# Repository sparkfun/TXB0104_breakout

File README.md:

SparkFun Voltage-Level Translator Breakout - TXB0104
================

[![SparkFun Voltage-Level Translator Breakout - TXB0104
](https://cdn.sparkfun.com//assets/parts/8/0/0/6/11771-01.jpg)](https://www.sparkfun.com/products/11771)

[SparkFun Voltage-Level Translator Breakout - TXB0104 (BOB-11771)](https://www.sparkfun.com/products/11771)

TI's bidirectional level translation IC.

Repository Contents
-------------------

* **/Hardware** - Eagle design files (.brd, .sch)
* **/Production** - Production panel files (.brd)

Documentation
--------------

* **[Hookup Guide](https://learn.sparkfun.com/tutorials/txb0104-level-shifter-hookup-guide)** - Basic hookup guide

License Information
-------------------

This product is _**open source**_! 

Please review the LICENSE.md file for license information. 

If you have any questions or concerns on licensing, please contact technical support on our [SparkFun forums](https://forum.sparkfun.com/viewforum.php?f=152).

Distributed as-is; no warranty is given.

- Your friends at SparkFun.

_<COLLABORATION CREDIT>_

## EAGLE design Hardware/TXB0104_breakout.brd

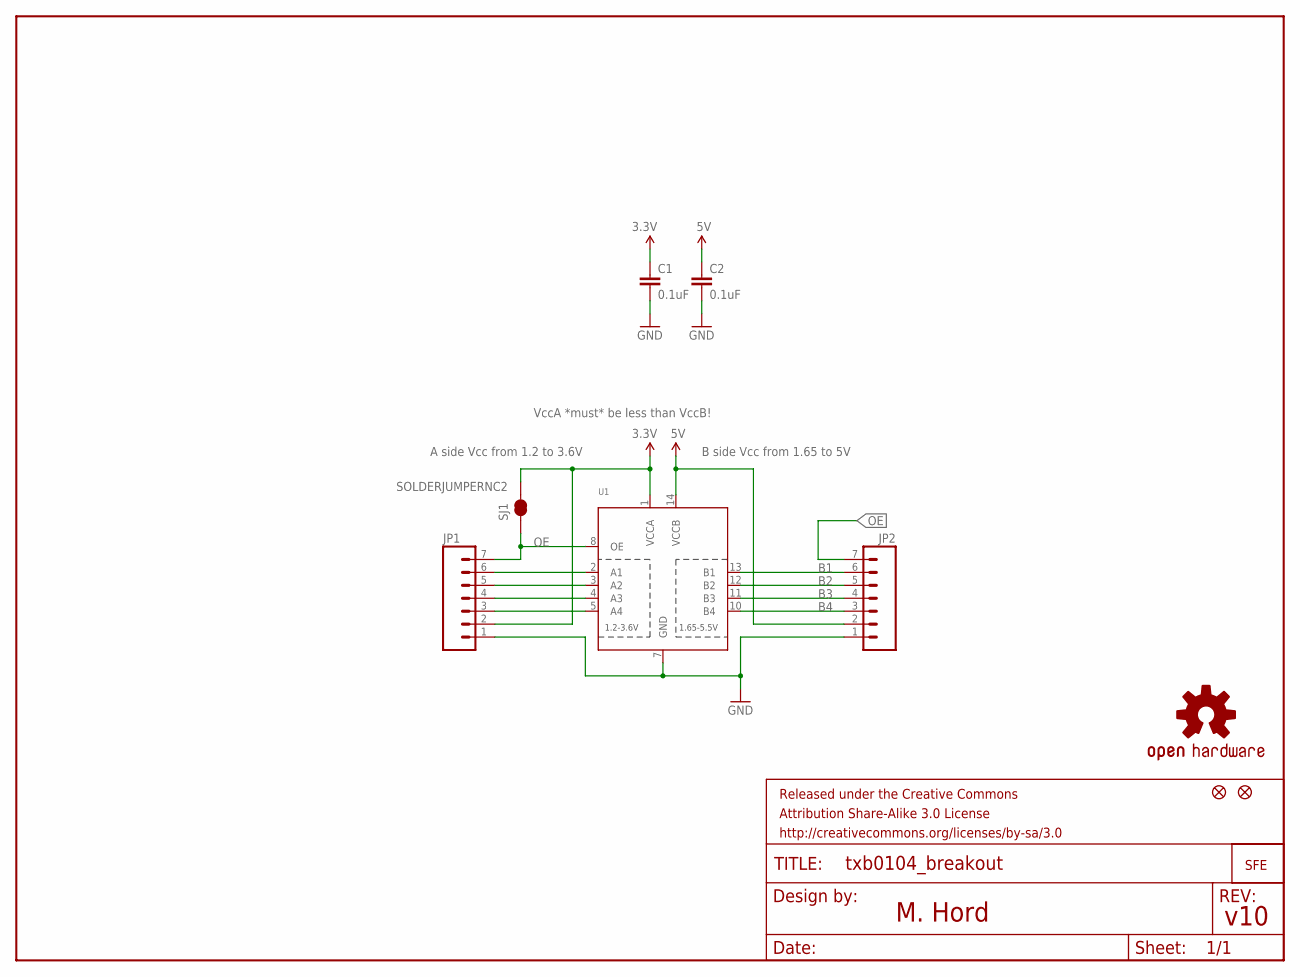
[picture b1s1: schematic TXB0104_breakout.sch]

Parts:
C1, C2: 0.1uF; 0603-CAP
FID1, FID2: FIDUCIALUFIDUCIAL; MICRO-FIDUCIAL
FRAME1: FRAME-LETTER; CREATIVE_COMMONS
JP1, JP2: M07; 1X07
LOGO1: LOGO-SFESK; SFE-LOGO-FLAME
LOGO2: OSHW-LOGOS; OSHW-LOGO-S
SJ1: SOLDERJUMPERNC2; SJ_2S-NOTRACE
U1: TXB0104PWRSOIC14; SO14

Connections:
3.3V: C1.1, JP1.2, SJ1.2, U1.1 (VCCA)
5V: C2.1, JP2.2, U1.14 (VCCB)
B1: JP2.6, U1.13 (B1)
B2: JP2.5, U1.12 (B2)
B3: JP2.4, U1.11 (B3)
B4: JP2.3, U1.10 (B4)
GND: C1.2, C2.2, JP1.1, JP2.1, U1.7 (GND)
unnamed: JP1.3, U1.5 (A4)
unnamed: JP1.4, U1.4 (A3)
unnamed: JP1.5, U1.3 (A2)
unnamed: JP1.6, U1.2 (A1)
OE: JP1.7, JP2.7, SJ1.1, U1.8 (OE)

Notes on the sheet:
A side Vcc from 1.2 to 3.6V
B side Vcc from 1.65 to 5V
VccA *must* be less than VccB!
v10
M. Hord

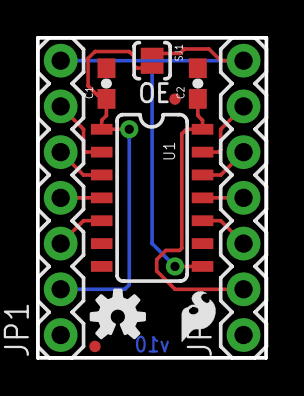
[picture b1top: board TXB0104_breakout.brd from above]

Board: 2 copper layers, 12.7 x 17.8 mm, 11 parts (0 on the bottom side), 12 nets.

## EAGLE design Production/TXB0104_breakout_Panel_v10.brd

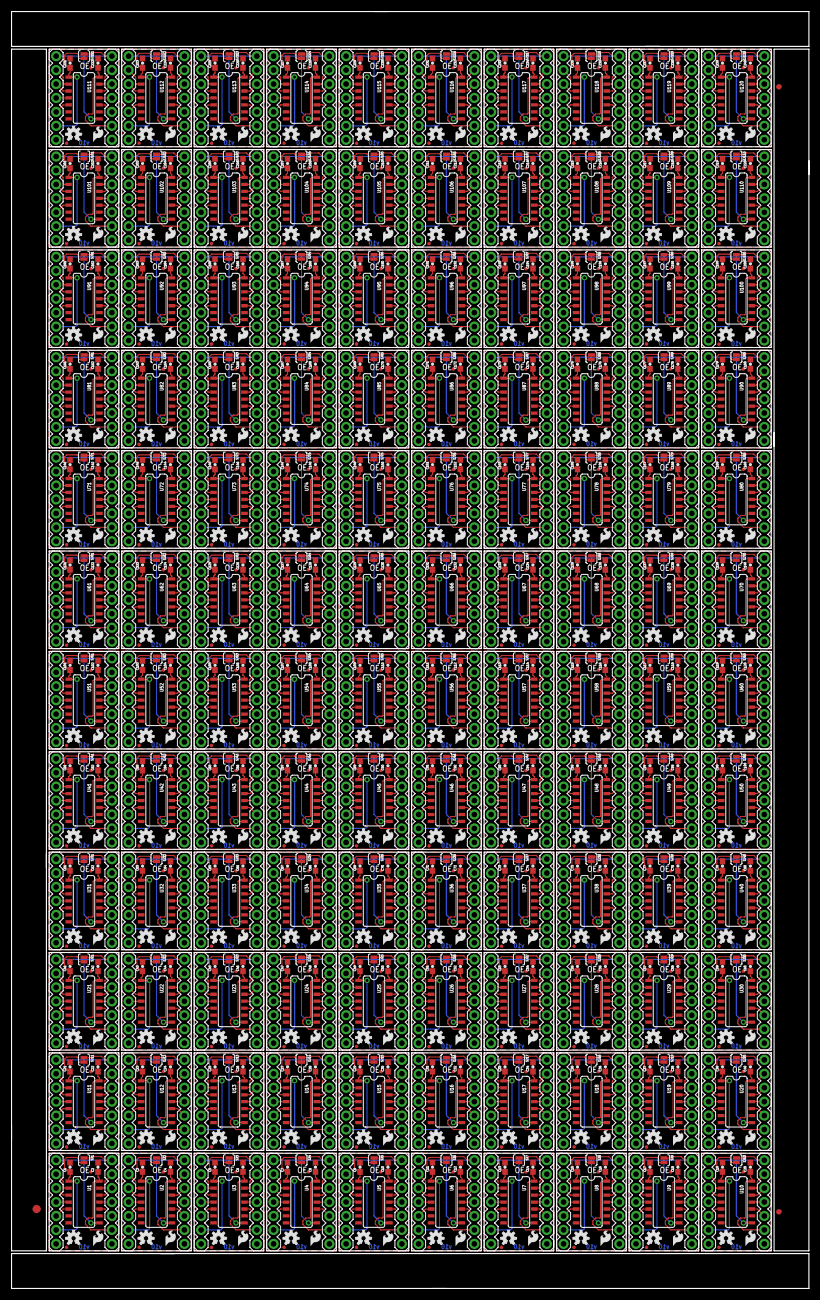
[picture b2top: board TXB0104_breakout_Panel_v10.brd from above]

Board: 2 copper layers, 145.3 x 232.7 mm, 1203 parts (0 on the bottom side), 1440 nets.

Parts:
C1, C2, C3, C4, C5, C6, C7, C8, C9, C10, C11, C12, C13, C14, C15, C16, C17, C18, C19, C20, C21, C22, C23, C24, C25, C26, C27, C28, C29, C30, C31, C32, C33, C34, C35, C36, C37, C38, C39, C40, C41, C42, C43, C44, C45, C46, C47, C48, C49, C50, C51, C52, C53, C54, C55, C56, C57, C58, C59, C60, C61, C62, C63, C64, C65, C66, C67, C68, C69, C70, C71, C72, C73, C74, C75, C76, C77, C78, C79, C80, C81, C82, C83, C84, C85, C86, C87, C88, C89, C90, C91, C92, C93, C94, C95, C96, C97, C98, C99, C100, C101, C102, C103, C104, C105, C106, C107, C108, C109, C110, C111, C112, C113, C114, C115, C116, C117, C118, C119, C120, C121, C122, C123, C124, C125, C126, C127, C128, C129, C130, C131, C132, C133, C134, C135, C136, C137, C138, C139, C140, C141, C142, C143, C144, C145, C146, C147, C148, C149, C150, C151, C152, C153, C154, C155, C156, C157, C158, C159, C160, C161, C162, C163, C164, C165, C166, C167, C168, C169, C170, C171, C172, C173, C174, C175, C176, C177, C178, C179, C180, C181, C182, C183, C184, C185, C186, C187, C188, C189, C190, C191, C192, C193, C194, C195, C196, C197, C198, C199, C200, C201, C202, C203, C204, C205, C206, C207, C208, C209, C210, C211, C212, C213, C214, C215, C216, C217, C218, C219, C220, C221, C222, C223, C224, C225, C226, C227, C228, C229, C230, C231, C232, C233, C234, C235, C236, C237, C238, C239, C240: 0.1uF; 0603-CAP
E$1: FIDUCIAL-1.5X3
E$7, E$8: FIDUCIAL-1X2
FID1, FID2, FID3, FID4, FID5, FID6, FID7, FID8, FID9, FID10, FID11, FID12, FID13, FID14, FID15, FID16, FID17, FID18, FID19, FID20, FID21, FID22, FID23, FID24, FID25, FID26, FID27, FID28, FID29, FID30, FID31, FID32, FID33, FID34, FID35, FID36, FID37, FID38, FID39, FID40, FID41, FID42, FID43, FID44, FID45, FID46, FID47, FID48, FID49, FID50, FID51, FID52, FID53, FID54, FID55, FID56, FID57, FID58, FID59, FID60, FID61, FID62, FID63, FID64, FID65, FID66, FID67, FID68, FID69, FID70, FID71, FID72, FID73, FID74, FID75, FID76, FID77, FID78, FID79, FID80, FID81, FID82, FID83, FID84, FID85, FID86, FID87, FID88, FID89, FID90, FID91, FID92, FID93, FID94, FID95, FID96, FID97, FID98, FID99, FID100, FID101, FID102, FID103, FID104, FID105, FID106, FID107, FID108, FID109, FID110, FID111, FID112, FID113, FID114, FID115, FID116, FID117, FID118, FID119, FID120, FID121, FID122, FID123, FID124, FID125, FID126, FID127, FID128, FID129, FID130, FID131, FID132, FID133, FID134, FID135, FID136, FID137, FID138, FID139, FID140, FID141, FID142, FID143, FID144, FID145, FID146, FID147, FID148, FID149, FID150, FID151, FID152, FID153, FID154, FID155, FID156, FID157, FID158, FID159, FID160, FID161, FID162, FID163, FID164, FID165, FID166, FID167, FID168, FID169, FID170, FID171, FID172, FID173, FID174, FID175, FID176, FID177, FID178, FID179, FID180, FID181, FID182, FID183, FID184, FID185, FID186, FID187, FID188, FID189, FID190, FID191, FID192, FID193, FID194, FID195, FID196, FID197, FID198, FID199, FID200, FID201, FID202, FID203, FID204, FID205, FID206, FID207, FID208, FID209, FID210, FID211, FID212, FID213, FID214, FID215, FID216, FID217, FID218, FID219, FID220, FID221, FID222, FID223, FID224, FID225, FID226, FID227, FID228, FID229, FID230, FID231, FID232, FID233, FID234, FID235, FID236, FID237, FID238, FID239, FID240: FIDUCIALUFIDUCIAL; MICRO-FIDUCIAL
JP1, JP2, JP3, JP4, JP5, JP6, JP7, JP8, JP9, JP10, JP11, JP12, JP13, JP14, JP15, JP16, JP17, JP18, JP19, JP20, JP21, JP22, JP23, JP24, JP25, JP26, JP27, JP28, JP29, JP30, JP31, JP32, JP33, JP34, JP35, JP36, JP37, JP38, JP39, JP40, JP41, JP42, JP43, JP44, JP45, JP46, JP47, JP48, JP49, JP50, JP51, JP52, JP53, JP54, JP55, JP56, JP57, JP58, JP59, JP60, JP61, JP62, JP63, JP64, JP65, JP66, JP67, JP68, JP69, JP70, JP71, JP72, JP73, JP74, JP75, JP76, JP77, JP78, JP79, JP80, JP81, JP82, JP83, JP84, JP85, JP86, JP87, JP88, JP89, JP90, JP91, JP92, JP93, JP94, JP95, JP96, JP97, JP98, JP99, JP100, JP101, JP102, JP103, JP104, JP105, JP106, JP107, JP108, JP109, JP110, JP111, JP112, JP113, JP114, JP115, JP116, JP117, JP118, JP119, JP120, JP121, JP122, JP123, JP124, JP125, JP126, JP127, JP128, JP129, JP130, JP131, JP132, JP133, JP134, JP135, JP136, JP137, JP138, JP139, JP140, JP141, JP142, JP143, JP144, JP145, JP146, JP147, JP148, JP149, JP150, JP151, JP152, JP153, JP154, JP155, JP156, JP157, JP158, JP159, JP160, JP161, JP162, JP163, JP164, JP165, JP166, JP167, JP168, JP169, JP170, JP171, JP172, JP173, JP174, JP175, JP176, JP177, JP178, JP179, JP180, JP181, JP182, JP183, JP184, JP185, JP186, JP187, JP188, JP189, JP190, JP191, JP192, JP193, JP194, JP195, JP196, JP197, JP198, JP199, JP200, JP201, JP202, JP203, JP204, JP205, JP206, JP207, JP208, JP209, JP210, JP211, JP212, JP213, JP214, JP215, JP216, JP217, JP218, JP219, JP220, JP221, JP222, JP223, JP224, JP225, JP226, JP227, JP228, JP229, JP230, JP231, JP232, JP233, JP234, JP235, JP236, JP237, JP238, JP239, JP240: 1X07
LOGO1, LOGO3, LOGO5, LOGO7, LOGO9, LOGO11, LOGO13, LOGO15, LOGO17, LOGO19, LOGO21, LOGO23, LOGO25, LOGO27, LOGO29, LOGO31, LOGO33, LOGO35, LOGO37, LOGO39, LOGO41, LOGO43, LOGO45, LOGO47, LOGO49, LOGO51, LOGO53, LOGO55, LOGO57, LOGO59, LOGO61, LOGO63, LOGO65, LOGO67, LOGO69, LOGO71, LOGO73, LOGO75, LOGO77, LOGO79, LOGO81, LOGO83, LOGO85, LOGO87, LOGO89, LOGO91, LOGO93, LOGO95, LOGO97, LOGO99, LOGO101, LOGO103, LOGO105, LOGO107, LOGO109, LOGO111, LOGO113, LOGO115, LOGO117, LOGO119, LOGO121, LOGO123, LOGO125, LOGO127, LOGO129, LOGO131, LOGO133, LOGO135, LOGO137, LOGO139, LOGO141, LOGO143, LOGO145, LOGO147, LOGO149, LOGO151, LOGO153, LOGO155, LOGO157, LOGO159, LOGO161, LOGO163, LOGO165, LOGO167, LOGO169, LOGO171, LOGO173, LOGO175, LOGO177, LOGO179, LOGO181, LOGO183, LOGO185, LOGO187, LOGO189, LOGO191, LOGO193, LOGO195, LOGO197, LOGO199, LOGO201, LOGO203, LOGO205, LOGO207, LOGO209, LOGO211, LOGO213, LOGO215, LOGO217, LOGO219, LOGO221, LOGO223, LOGO225, LOGO227, LOGO229, LOGO231, LOGO233, LOGO235, LOGO237, LOGO239: LOGO-SFESK; SFE-LOGO-FLAME
LOGO2, LOGO4, LOGO6, LOGO8, LOGO10, LOGO12, LOGO14, LOGO16, LOGO18, LOGO20, LOGO22, LOGO24, LOGO26, LOGO28, LOGO30, LOGO32, LOGO34, LOGO36, LOGO38, LOGO40, LOGO42, LOGO44, LOGO46, LOGO48, LOGO50, LOGO52, LOGO54, LOGO56, LOGO58, LOGO60, LOGO62, LOGO64, LOGO66, LOGO68, LOGO70, LOGO72, LOGO74, LOGO76, LOGO78, LOGO80, LOGO82, LOGO84, LOGO86, LOGO88, LOGO90, LOGO92, LOGO94, LOGO96, LOGO98, LOGO100, LOGO102, LOGO104, LOGO106, LOGO108, LOGO110, LOGO112, LOGO114, LOGO116, LOGO118, LOGO120, LOGO122, LOGO124, LOGO126, LOGO128, LOGO130, LOGO132, LOGO134, LOGO136, LOGO138, LOGO140, LOGO142, LOGO144, LOGO146, LOGO148, LOGO150, LOGO152, LOGO154, LOGO156, LOGO158, LOGO160, LOGO162, LOGO164, LOGO166, LOGO168, LOGO170, LOGO172, LOGO174, LOGO176, LOGO178, LOGO180, LOGO182, LOGO184, LOGO186, LOGO188, LOGO190, LOGO192, LOGO194, LOGO196, LOGO198, LOGO200, LOGO202, LOGO204, LOGO206, LOGO208, LOGO210, LOGO212, LOGO214, LOGO216, LOGO218, LOGO220, LOGO222, LOGO224, LOGO226, LOGO228, LOGO230, LOGO232, LOGO234, LOGO236, LOGO238, LOGO240: OSHW-LOGOS; OSHW-LOGO-S
SJ1, SJ2, SJ3, SJ4, SJ5, SJ6, SJ7, SJ8, SJ9, SJ10, SJ11, SJ12, SJ13, SJ14, SJ15, SJ16, SJ17, SJ18, SJ19, SJ20, SJ21, SJ22, SJ23, SJ24, SJ25, SJ26, SJ27, SJ28, SJ29, SJ30, SJ31, SJ32, SJ33, SJ34, SJ35, SJ36, SJ37, SJ38, SJ39, SJ40, SJ41, SJ42, SJ43, SJ44, SJ45, SJ46, SJ47, SJ48, SJ49, SJ50, SJ51, SJ52, SJ53, SJ54, SJ55, SJ56, SJ57, SJ58, SJ59, SJ60, SJ61, SJ62, SJ63, SJ64, SJ65, SJ66, SJ67, SJ68, SJ69, SJ70, SJ71, SJ72, SJ73, SJ74, SJ75, SJ76, SJ77, SJ78, SJ79, SJ80, SJ81, SJ82, SJ83, SJ84, SJ85, SJ86, SJ87, SJ88, SJ89, SJ90, SJ91, SJ92, SJ93, SJ94, SJ95, SJ96, SJ97, SJ98, SJ99, SJ100, SJ101, SJ102, SJ103, SJ104, SJ105, SJ106, SJ107, SJ108, SJ109, SJ110, SJ111, SJ112, SJ113, SJ114, SJ115, SJ116, SJ117, SJ118, SJ119, SJ120: SOLDERJUMPERNC2; SJ_2S-NOTRACE
U1, U2, U3, U4, U5, U6, U7, U8, U9, U10, U11, U12, U13, U14, U15, U16, U17, U18, U19, U20, U21, U22, U23, U24, U25, U26, U27, U28, U29, U30, U31, U32, U33, U34, U35, U36, U37, U38, U39, U40, U41, U42, U43, U44, U45, U46, U47, U48, U49, U50, U51, U52, U53, U54, U55, U56, U57, U58, U59, U60, U61, U62, U63, U64, U65, U66, U67, U68, U69, U70, U71, U72, U73, U74, U75, U76, U77, U78, U79, U80, U81, U82, U83, U84, U85, U86, U87, U88, U89, U90, U91, U92, U93, U94, U95, U96, U97, U98, U99, U100, U101, U102, U103, U104, U105, U106, U107, U108, U109, U110, U111, U112, U113, U114, U115, U116, U117, U118, U119, U120: SO14

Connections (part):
3.3V: C1.1, JP1.2, SJ1.2, U1.1
3.3V1: C3.1, JP3.2, SJ2.2, U2.1
3.3V2: C5.1, JP5.2, SJ3.2, U3.1
3.3V3: C7.1, JP7.2, SJ4.2, U4.1
3.3V4: C9.1, JP9.2, SJ5.2, U5.1
3.3V5: C11.1, JP11.2, SJ6.2, U6.1
3.3V6: C13.1, JP13.2, SJ7.2, U7.1
3.3V7: C15.1, JP15.2, SJ8.2, U8.1
3.3V8: C17.1, JP17.2, SJ9.2, U9.1
3.3V9: C19.1, JP19.2, SJ10.2, U10.1
3.3V10: C21.1, JP21.2, SJ11.2, U11.1
3.3V11: C23.1, JP23.2, SJ12.2, U12.1
3.3V12: C25.1, JP25.2, SJ13.2, U13.1
3.3V13: C27.1, JP27.2, SJ14.2, U14.1
3.3V14: C29.1, JP29.2, SJ15.2, U15.1
3.3V15: C31.1, JP31.2, SJ16.2, U16.1
3.3V16: C33.1, JP33.2, SJ17.2, U17.1
3.3V17: C35.1, JP35.2, SJ18.2, U18.1
3.3V18: C37.1, JP37.2, SJ19.2, U19.1
3.3V19: C39.1, JP39.2, SJ20.2, U20.1
3.3V20: C41.1, JP41.2, SJ21.2, U21.1
3.3V21: C43.1, JP43.2, SJ22.2, U22.1
3.3V22: C45.1, JP45.2, SJ23.2, U23.1
3.3V23: C47.1, JP47.2, SJ24.2, U24.1
3.3V24: C49.1, JP49.2, SJ25.2, U25.1
3.3V25: C51.1, JP51.2, SJ26.2, U26.1
3.3V26: C53.1, JP53.2, SJ27.2, U27.1
3.3V27: C55.1, JP55.2, SJ28.2, U28.1
3.3V28: C57.1, JP57.2, SJ29.2, U29.1
3.3V29: C59.1, JP59.2, SJ30.2, U30.1
3.3V30: C61.1, JP61.2, SJ31.2, U31.1
3.3V31: C63.1, JP63.2, SJ32.2, U32.1
3.3V32: C65.1, JP65.2, SJ33.2, U33.1
3.3V33: C67.1, JP67.2, SJ34.2, U34.1
3.3V34: C69.1, JP69.2, SJ35.2, U35.1
3.3V35: C71.1, JP71.2, SJ36.2, U36.1
3.3V36: C73.1, JP73.2, SJ37.2, U37.1
3.3V37: C75.1, JP75.2, SJ38.2, U38.1
3.3V38: C77.1, JP77.2, SJ39.2, U39.1
3.3V39: C79.1, JP79.2, SJ40.2, U40.1
3.3V40: C81.1, JP81.2, SJ41.2, U41.1
3.3V41: C83.1, JP83.2, SJ42.2, U42.1
3.3V42: C85.1, JP85.2, SJ43.2, U43.1
3.3V43: C87.1, JP87.2, SJ44.2, U44.1
3.3V44: C89.1, JP89.2, SJ45.2, U45.1
3.3V45: C91.1, JP91.2, SJ46.2, U46.1
3.3V46: C93.1, JP93.2, SJ47.2, U47.1
3.3V47: C95.1, JP95.2, SJ48.2, U48.1
3.3V48: C97.1, JP97.2, SJ49.2, U49.1
3.3V49: C99.1, JP99.2, SJ50.2, U50.1
3.3V50: C101.1, JP101.2, SJ51.2, U51.1
3.3V51: C103.1, JP103.2, SJ52.2, U52.1
3.3V52: C105.1, JP105.2, SJ53.2, U53.1
3.3V53: C107.1, JP107.2, SJ54.2, U54.1
3.3V54: C109.1, JP109.2, SJ55.2, U55.1
3.3V55: C111.1, JP111.2, SJ56.2, U56.1
3.3V56: C113.1, JP113.2, SJ57.2, U57.1
3.3V57: C115.1, JP115.2, SJ58.2, U58.1
3.3V58: C117.1, JP117.2, SJ59.2, U59.1
3.3V59: C119.1, JP119.2, SJ60.2, U60.1
3.3V60: C121.1, JP121.2, SJ61.2, U61.1
3.3V61: C123.1, JP123.2, SJ62.2, U62.1
3.3V62: C125.1, JP125.2, SJ63.2, U63.1
3.3V63: C127.1, JP127.2, SJ64.2, U64.1
3.3V64: C129.1, JP129.2, SJ65.2, U65.1
3.3V65: C131.1, JP131.2, SJ66.2, U66.1
3.3V66: C133.1, JP133.2, SJ67.2, U67.1
3.3V67: C135.1, JP135.2, SJ68.2, U68.1
3.3V68: C137.1, JP137.2, SJ69.2, U69.1
3.3V69: C139.1, JP139.2, SJ70.2, U70.1
3.3V70: C141.1, JP141.2, SJ71.2, U71.1
3.3V71: C143.1, JP143.2, SJ72.2, U72.1
3.3V72: C145.1, JP145.2, SJ73.2, U73.1
3.3V73: C147.1, JP147.2, SJ74.2, U74.1
3.3V74: C149.1, JP149.2, SJ75.2, U75.1
3.3V75: C151.1, JP151.2, SJ76.2, U76.1
3.3V76: C153.1, JP153.2, SJ77.2, U77.1
3.3V77: C155.1, JP155.2, SJ78.2, U78.1
3.3V78: C157.1, JP157.2, SJ79.2, U79.1
3.3V79: C159.1, JP159.2, SJ80.2, U80.1
3.3V80: C161.1, JP161.2, SJ81.2, U81.1
3.3V81: C163.1, JP163.2, SJ82.2, U82.1
3.3V82: C165.1, JP165.2, SJ83.2, U83.1
3.3V83: C167.1, JP167.2, SJ84.2, U84.1
3.3V84: C169.1, JP169.2, SJ85.2, U85.1
3.3V85: C171.1, JP171.2, SJ86.2, U86.1
3.3V86: C173.1, JP173.2, SJ87.2, U87.1
3.3V87: C175.1, JP175.2, SJ88.2, U88.1
3.3V88: C177.1, JP177.2, SJ89.2, U89.1
3.3V89: C179.1, JP179.2, SJ90.2, U90.1
3.3V90: C181.1, JP181.2, SJ91.2, U91.1
3.3V91: C183.1, JP183.2, SJ92.2, U92.1
3.3V92: C185.1, JP185.2, SJ93.2, U93.1
3.3V93: C187.1, JP187.2, SJ94.2, U94.1
3.3V94: C189.1, JP189.2, SJ95.2, U95.1
3.3V95: C191.1, JP191.2, SJ96.2, U96.1
3.3V96: C193.1, JP193.2, SJ97.2, U97.1
3.3V97: C195.1, JP195.2, SJ98.2, U98.1
3.3V98: C197.1, JP197.2, SJ99.2, U99.1
3.3V99: C199.1, JP199.2, SJ100.2, U100.1
3.3V100: C201.1, JP201.2, SJ101.2, U101.1
3.3V101: C203.1, JP203.2, SJ102.2, U102.1
3.3V102: C205.1, JP205.2, SJ103.2, U103.1
3.3V103: C207.1, JP207.2, SJ104.2, U104.1
3.3V104: C209.1, JP209.2, SJ105.2, U105.1
3.3V105: C211.1, JP211.2, SJ106.2, U106.1
3.3V106: C213.1, JP213.2, SJ107.2, U107.1
3.3V107: C215.1, JP215.2, SJ108.2, U108.1
3.3V108: C217.1, JP217.2, SJ109.2, U109.1
3.3V109: C219.1, JP219.2, SJ110.2, U110.1
3.3V110: C221.1, JP221.2, SJ111.2, U111.1
3.3V111: C223.1, JP223.2, SJ112.2, U112.1
3.3V112: C225.1, JP225.2, SJ113.2, U113.1
3.3V113: C227.1, JP227.2, SJ114.2, U114.1
3.3V114: C229.1, JP229.2, SJ115.2, U115.1
3.3V115: C231.1, JP231.2, SJ116.2, U116.1
3.3V116: C233.1, JP233.2, SJ117.2, U117.1
3.3V117: C235.1, JP235.2, SJ118.2, U118.1
3.3V118: C237.1, JP237.2, SJ119.2, U119.1
3.3V119: C239.1, JP239.2, SJ120.2, U120.1
5V: C2.1, JP2.2, U1.14
5V1: C4.1, JP4.2, U2.14
5V2: C6.1, JP6.2, U3.14
5V3: C8.1, JP8.2, U4.14
5V4: C10.1, JP10.2, U5.14
5V5: C12.1, JP12.2, U6.14
5V6: C14.1, JP14.2, U7.14
5V7: C16.1, JP16.2, U8.14
5V8: C18.1, JP18.2, U9.14
5V9: C20.1, JP20.2, U10.14
5V10: C22.1, JP22.2, U11.14
5V11: C24.1, JP24.2, U12.14
5V12: C26.1, JP26.2, U13.14
5V13: C28.1, JP28.2, U14.14
5V14: C30.1, JP30.2, U15.14
5V15: C32.1, JP32.2, U16.14
5V16: C34.1, JP34.2, U17.14
5V17: C36.1, JP36.2, U18.14
5V18: C38.1, JP38.2, U19.14
5V19: C40.1, JP40.2, U20.14
5V20: C42.1, JP42.2, U21.14
5V21: C44.1, JP44.2, U22.14
5V22: C46.1, JP46.2, U23.14
5V23: C48.1, JP48.2, U24.14
5V24: C50.1, JP50.2, U25.14
5V25: C52.1, JP52.2, U26.14
5V26: C54.1, JP54.2, U27.14
5V27: C56.1, JP56.2, U28.14
5V28: C58.1, JP58.2, U29.14
5V29: C60.1, JP60.2, U30.14
5V30: C62.1, JP62.2, U31.14
5V31: C64.1, JP64.2, U32.14
5V32: C66.1, JP66.2, U33.14
5V33: C68.1, JP68.2, U34.14
5V34: C70.1, JP70.2, U35.14
5V35: C72.1, JP72.2, U36.14
5V36: C74.1, JP74.2, U37.14
5V37: C76.1, JP76.2, U38.14
5V38: C78.1, JP78.2, U39.14
5V39: C80.1, JP80.2, U40.14
5V40: C82.1, JP82.2, U41.14
5V41: C84.1, JP84.2, U42.14
5V42: C86.1, JP86.2, U43.14
5V43: C88.1, JP88.2, U44.14
5V44: C90.1, JP90.2, U45.14
5V45: C92.1, JP92.2, U46.14
5V46: C94.1, JP94.2, U47.14
5V47: C96.1, JP96.2, U48.14
5V48: C98.1, JP98.2, U49.14
5V49: C100.1, JP100.2, U50.14
5V50: C102.1, JP102.2, U51.14
5V51: C104.1, JP104.2, U52.14
5V52: C106.1, JP106.2, U53.14
5V53: C108.1, JP108.2, U54.14
5V54: C110.1, JP110.2, U55.14
5V55: C112.1, JP112.2, U56.14
5V56: C114.1, JP114.2, U57.14
5V57: C116.1, JP116.2, U58.14
5V58: C118.1, JP118.2, U59.14
5V59: C120.1, JP120.2, U60.14
5V60: C122.1, JP122.2, U61.14
5V61: C124.1, JP124.2, U62.14
5V62: C126.1, JP126.2, U63.14
5V63: C128.1, JP128.2, U64.14
5V64: C130.1, JP130.2, U65.14
5V65: C132.1, JP132.2, U66.14
5V66: C134.1, JP134.2, U67.14
5V67: C136.1, JP136.2, U68.14
5V68: C138.1, JP138.2, U69.14
5V69: C140.1, JP140.2, U70.14
5V70: C142.1, JP142.2, U71.14
5V71: C144.1, JP144.2, U72.14
5V72: C146.1, JP146.2, U73.14
5V73: C148.1, JP148.2, U74.14
5V74: C150.1, JP150.2, U75.14
5V75: C152.1, JP152.2, U76.14
5V76: C154.1, JP154.2, U77.14
5V77: C156.1, JP156.2, U78.14
5V78: C158.1, JP158.2, U79.14
5V79: C160.1, JP160.2, U80.14
5V80: C162.1, JP162.2, U81.14
5V81: C164.1, JP164.2, U82.14
5V82: C166.1, JP166.2, U83.14
5V83: C168.1, JP168.2, U84.14
5V84: C170.1, JP170.2, U85.14
5V85: C172.1, JP172.2, U86.14
5V86: C174.1, JP174.2, U87.14
5V87: C176.1, JP176.2, U88.14
5V88: C178.1, JP178.2, U89.14
5V89: C180.1, JP180.2, U90.14
5V90: C182.1, JP182.2, U91.14
5V91: C184.1, JP184.2, U92.14
5V92: C186.1, JP186.2, U93.14
5V93: C188.1, JP188.2, U94.14
5V94: C190.1, JP190.2, U95.14
5V95: C192.1, JP192.2, U96.14
5V96: C194.1, JP194.2, U97.14
5V97: C196.1, JP196.2, U98.14
5V98: C198.1, JP198.2, U99.14
5V99: C200.1, JP200.2, U100.14
5V100: C202.1, JP202.2, U101.14
5V101: C204.1, JP204.2, U102.14
5V102: C206.1, JP206.2, U103.14
5V103: C208.1, JP208.2, U104.14
5V104: C210.1, JP210.2, U105.14
5V105: C212.1, JP212.2, U106.14
5V106: C214.1, JP214.2, U107.14
5V107: C216.1, JP216.2, U108.14
5V108: C218.1, JP218.2, U109.14
5V109: C220.1, JP220.2, U110.14
5V110: C222.1, JP222.2, U111.14
5V111: C224.1, JP224.2, U112.14
5V112: C226.1, JP226.2, U113.14
5V113: C228.1, JP228.2, U114.14
5V114: C230.1, JP230.2, U115.14
5V115: C232.1, JP232.2, U116.14
5V116: C234.1, JP234.2, U117.14
5V117: C236.1, JP236.2, U118.14
5V118: C238.1, JP238.2, U119.14
5V119: C240.1, JP240.2, U120.14
B1: JP2.6, U1.13
B2: JP2.5, U1.12
B3: JP2.4, U1.11
B4: JP2.3, U1.10
B5: JP4.6, U2.13
B6: JP4.5, U2.12
B7: JP4.4, U2.11
B8: JP4.3, U2.10
B9: JP6.6, U3.13
B10: JP6.5, U3.12
B11: JP6.4, U3.11
B12: JP6.3, U3.10
B13: JP8.6, U4.13
B14: JP8.5, U4.12
B15: JP8.4, U4.11
B16: JP8.3, U4.10
B17: JP10.6, U5.13
B18: JP10.5, U5.12
B19: JP10.4, U5.11
B20: JP10.3, U5.10
B21: JP12.6, U6.13
B22: JP12.5, U6.12
B23: JP12.4, U6.11
B24: JP12.3, U6.10
B25: JP14.6, U7.13
B26: JP14.5, U7.12
B27: JP14.4, U7.11
B28: JP14.3, U7.10
B29: JP16.6, U8.13
B30: JP16.5, U8.12
B31: JP16.4, U8.11
B32: JP16.3, U8.10
B33: JP18.6, U9.13
B34: JP18.5, U9.12
B35: JP18.4, U9.11
B36: JP18.3, U9.10
B37: JP20.6, U10.13
B38: JP20.5, U10.12
B39: JP20.4, U10.11
B40: JP20.3, U10.10
B41: JP22.6, U11.13
B42: JP22.5, U11.12
B43: JP22.4, U11.11
B44: JP22.3, U11.10
B45: JP24.6, U12.13
B46: JP24.5, U12.12
B47: JP24.4, U12.11
B48: JP24.3, U12.10
B49: JP26.6, U13.13
B50: JP26.5, U13.12
B51: JP26.4, U13.11
B52: JP26.3, U13.10
B53: JP28.6, U14.13
B54: JP28.5, U14.12
B55: JP28.4, U14.11
B56: JP28.3, U14.10
B57: JP30.6, U15.13
B58: JP30.5, U15.12
B59: JP30.4, U15.11
B60: JP30.3, U15.10
B61: JP32.6, U16.13
B62: JP32.5, U16.12
B63: JP32.4, U16.11
B64: JP32.3, U16.10
B65: JP34.6, U17.13
B66: JP34.5, U17.12
B67: JP34.4, U17.11
B68: JP34.3, U17.10
B69: JP36.6, U18.13
B70: JP36.5, U18.12
B71: JP36.4, U18.11
B72: JP36.3, U18.10
B73: JP38.6, U19.13
B74: JP38.5, U19.12
B75: JP38.4, U19.11
B76: JP38.3, U19.10
B77: JP40.6, U20.13
B78: JP40.5, U20.12
B79: JP40.4, U20.11
B80: JP40.3, U20.10
B81: JP42.6, U21.13
B82: JP42.5, U21.12
B83: JP42.4, U21.11
B84: JP42.3, U21.10
B85: JP44.6, U22.13
B86: JP44.5, U22.12
B87: JP44.4, U22.11
B88: JP44.3, U22.10
B89: JP46.6, U23.13
B90: JP46.5, U23.12
B91: JP46.4, U23.11
B92: JP46.3, U23.10
B93: JP48.6, U24.13
B94: JP48.5, U24.12
B95: JP48.4, U24.11
B96: JP48.3, U24.10
B97: JP50.6, U25.13
B98: JP50.5, U25.12
B99: JP50.4, U25.11
B100: JP50.3, U25.10
B101: JP52.6, U26.13
B102: JP52.5, U26.12
B103: JP52.4, U26.11
B104: JP52.3, U26.10
B105: JP54.6, U27.13
B106: JP54.5, U27.12
B107: JP54.4, U27.11
B108: JP54.3, U27.10
B109: JP56.6, U28.13
B110: JP56.5, U28.12
B111: JP56.4, U28.11
B112: JP56.3, U28.10
B113: JP58.6, U29.13
B114: JP58.5, U29.12
B115: JP58.4, U29.11
B116: JP58.3, U29.10
B117: JP60.6, U30.13
B118: JP60.5, U30.12
B119: JP60.4, U30.11
B120: JP60.3, U30.10
B121: JP62.6, U31.13
B122: JP62.5, U31.12
B123: JP62.4, U31.11
B124: JP62.3, U31.10
B125: JP64.6, U32.13
B126: JP64.5, U32.12
B127: JP64.4, U32.11
B128: JP64.3, U32.10
B129: JP66.6, U33.13
B130: JP66.5, U33.12
B131: JP66.4, U33.11
B132: JP66.3, U33.10
B133: JP68.6, U34.13
B134: JP68.5, U34.12
B135: JP68.4, U34.11
B136: JP68.3, U34.10
B137: JP70.6, U35.13
B138: JP70.5, U35.12
B139: JP70.4, U35.11
B140: JP70.3, U35.10
B141: JP72.6, U36.13
B142: JP72.5, U36.12
B143: JP72.4, U36.11
B144: JP72.3, U36.10
B145: JP74.6, U37.13
B146: JP74.5, U37.12
B147: JP74.4, U37.11
B148: JP74.3, U37.10
B149: JP76.6, U38.13
B150: JP76.5, U38.12
B151: JP76.4, U38.11
B152: JP76.3, U38.10
B153: JP78.6, U39.13
B154: JP78.5, U39.12
B155: JP78.4, U39.11
B156: JP78.3, U39.10
B157: JP80.6, U40.13
B158: JP80.5, U40.12
B159: JP80.4, U40.11
B160: JP80.3, U40.10
B161: JP82.6, U41.13
B162: JP82.5, U41.12
B163: JP82.4, U41.11
B164: JP82.3, U41.10
B165: JP84.6, U42.13
B166: JP84.5, U42.12
B167: JP84.4, U42.11
B168: JP84.3, U42.10
B169: JP86.6, U43.13
B170: JP86.5, U43.12
B171: JP86.4, U43.11
B172: JP86.3, U43.10
B173: JP88.6, U44.13
B174: JP88.5, U44.12
B175: JP88.4, U44.11
B176: JP88.3, U44.10
B177: JP90.6, U45.13
B178: JP90.5, U45.12
B179: JP90.4, U45.11
B180: JP90.3, U45.10
B181: JP92.6, U46.13
B182: JP92.5, U46.12
B183: JP92.4, U46.11
B184: JP92.3, U46.10
B185: JP94.6, U47.13
B186: JP94.5, U47.12
B187: JP94.4, U47.11
B188: JP94.3, U47.10
B189: JP96.6, U48.13
B190: JP96.5, U48.12
B191: JP96.4, U48.11
B192: JP96.3, U48.10
B193: JP98.6, U49.13
B194: JP98.5, U49.12
B195: JP98.4, U49.11
B196: JP98.3, U49.10
B197: JP100.6, U50.13
B198: JP100.5, U50.12
B199: JP100.4, U50.11
B200: JP100.3, U50.10
B201: JP102.6, U51.13
B202: JP102.5, U51.12
B203: JP102.4, U51.11
B204: JP102.3, U51.10
B205: JP104.6, U52.13
B206: JP104.5, U52.12
B207: JP104.4, U52.11
B208: JP104.3, U52.10
B209: JP106.6, U53.13
B210: JP106.5, U53.12
B211: JP106.4, U53.11
B212: JP106.3, U53.10
B213: JP108.6, U54.13
B214: JP108.5, U54.12
B215: JP108.4, U54.11
B216: JP108.3, U54.10
B217: JP110.6, U55.13
B218: JP110.5, U55.12
B219: JP110.4, U55.11
B220: JP110.3, U55.10
B221: JP112.6, U56.13
B222: JP112.5, U56.12
B223: JP112.4, U56.11
B224: JP112.3, U56.10
B225: JP114.6, U57.13
B226: JP114.5, U57.12
B227: JP114.4, U57.11
B228: JP114.3, U57.10
B229: JP116.6, U58.13
B230: JP116.5, U58.12
B231: JP116.4, U58.11
B232: JP116.3, U58.10
B233: JP118.6, U59.13
B234: JP118.5, U59.12
B235: JP118.4, U59.11
B236: JP118.3, U59.10
B237: JP120.6, U60.13
B238: JP120.5, U60.12
B239: JP120.4, U60.11
B240: JP120.3, U60.10
B241: JP122.6, U61.13
B242: JP122.5, U61.12
B243: JP122.4, U61.11
B244: JP122.3, U61.10
B245: JP124.6, U62.13
B246: JP124.5, U62.12
B247: JP124.4, U62.11
B248: JP124.3, U62.10
B249: JP126.6, U63.13
B250: JP126.5, U63.12
B251: JP126.4, U63.11
B252: JP126.3, U63.10
B253: JP128.6, U64.13
B254: JP128.5, U64.12
B255: JP128.4, U64.11
B256: JP128.3, U64.10
B257: JP130.6, U65.13
B258: JP130.5, U65.12
B259: JP130.4, U65.11
B260: JP130.3, U65.10
B261: JP132.6, U66.13
B262: JP132.5, U66.12
B263: JP132.4, U66.11
B264: JP132.3, U66.10
B265: JP134.6, U67.13
B266: JP134.5, U67.12
B267: JP134.4, U67.11
B268: JP134.3, U67.10
B269: JP136.6, U68.13
B270: JP136.5, U68.12
B271: JP136.4, U68.11
B272: JP136.3, U68.10
B273: JP138.6, U69.13
B274: JP138.5, U69.12
B275: JP138.4, U69.11
B276: JP138.3, U69.10
B277: JP140.6, U70.13
B278: JP140.5, U70.12
B279: JP140.4, U70.11
B280: JP140.3, U70.10
B281: JP142.6, U71.13
B282: JP142.5, U71.12
B283: JP142.4, U71.11
B284: JP142.3, U71.10
B285: JP144.6, U72.13
B286: JP144.5, U72.12
B287: JP144.4, U72.11
B288: JP144.3, U72.10
B289: JP146.6, U73.13
B290: JP146.5, U73.12
B291: JP146.4, U73.11
B292: JP146.3, U73.10
B293: JP148.6, U74.13
B294: JP148.5, U74.12
B295: JP148.4, U74.11
B296: JP148.3, U74.10
B297: JP150.6, U75.13
B298: JP150.5, U75.12
B299: JP150.4, U75.11
B300: JP150.3, U75.10
B301: JP152.6, U76.13
B302: JP152.5, U76.12
B303: JP152.4, U76.11
B304: JP152.3, U76.10
B305: JP154.6, U77.13
B306: JP154.5, U77.12
B307: JP154.4, U77.11
B308: JP154.3, U77.10
B309: JP156.6, U78.13
B310: JP156.5, U78.12
B311: JP156.4, U78.11
B312: JP156.3, U78.10
B313: JP158.6, U79.13
B314: JP158.5, U79.12
B315: JP158.4, U79.11
B316: JP158.3, U79.10
B317: JP160.6, U80.13
B318: JP160.5, U80.12
B319: JP160.4, U80.11
B320: JP160.3, U80.10
B321: JP162.6, U81.13
B322: JP162.5, U81.12
B323: JP162.4, U81.11
B324: JP162.3, U81.10
B325: JP164.6, U82.13
B326: JP164.5, U82.12
B327: JP164.4, U82.11
B328: JP164.3, U82.10
B329: JP166.6, U83.13
B330: JP166.5, U83.12
B331: JP166.4, U83.11
B332: JP166.3, U83.10
B333: JP168.6, U84.13
B334: JP168.5, U84.12
B335: JP168.4, U84.11
B336: JP168.3, U84.10
B337: JP170.6, U85.13
B338: JP170.5, U85.12
B339: JP170.4, U85.11
B340: JP170.3, U85.10
B341: JP172.6, U86.13
B342: JP172.5, U86.12
B343: JP172.4, U86.11
B344: JP172.3, U86.10
B345: JP174.6, U87.13
B346: JP174.5, U87.12
B347: JP174.4, U87.11
B348: JP174.3, U87.10
B349: JP176.6, U88.13
B350: JP176.5, U88.12
B351: JP176.4, U88.11
B352: JP176.3, U88.10
B353: JP178.6, U89.13
B354: JP178.5, U89.12
B355: JP178.4, U89.11
B356: JP178.3, U89.10
B357: JP180.6, U90.13
B358: JP180.5, U90.12
B359: JP180.4, U90.11
B360: JP180.3, U90.10
B361: JP182.6, U91.13
B362: JP182.5, U91.12
B363: JP182.4, U91.11
B364: JP182.3, U91.10
B365: JP184.6, U92.13
B366: JP184.5, U92.12
B367: JP184.4, U92.11
B368: JP184.3, U92.10
B369: JP186.6, U93.13
B370: JP186.5, U93.12
B371: JP186.4, U93.11
B372: JP186.3, U93.10
B373: JP188.6, U94.13
B374: JP188.5, U94.12
B375: JP188.4, U94.11
B376: JP188.3, U94.10
B377: JP190.6, U95.13
B378: JP190.5, U95.12
B379: JP190.4, U95.11
B380: JP190.3, U95.10
B381: JP192.6, U96.13
B382: JP192.5, U96.12
B383: JP192.4, U96.11
B384: JP192.3, U96.10
B385: JP194.6, U97.13
B386: JP194.5, U97.12
B387: JP194.4, U97.11
B388: JP194.3, U97.10
B389: JP196.6, U98.13
B390: JP196.5, U98.12
B391: JP196.4, U98.11
B392: JP196.3, U98.10
B393: JP198.6, U99.13
B394: JP198.5, U99.12
B395: JP198.4, U99.11
B396: JP198.3, U99.10
B397: JP200.6, U100.13
B398: JP200.5, U100.12
B399: JP200.4, U100.11
B400: JP200.3, U100.10
B401: JP202.6, U101.13
B402: JP202.5, U101.12
B403: JP202.4, U101.11
B404: JP202.3, U101.10
B405: JP204.6, U102.13
B406: JP204.5, U102.12
B407: JP204.4, U102.11
B408: JP204.3, U102.10
B409: JP206.6, U103.13
B410: JP206.5, U103.12
B411: JP206.4, U103.11
B412: JP206.3, U103.10
B413: JP208.6, U104.13
B414: JP208.5, U104.12
B415: JP208.4, U104.11
B416: JP208.3, U104.10
B417: JP210.6, U105.13
B418: JP210.5, U105.12
B419: JP210.4, U105.11
B420: JP210.3, U105.10
B421: JP212.6, U106.13
B422: JP212.5, U106.12
B423: JP212.4, U106.11
B424: JP212.3, U106.10
B425: JP214.6, U107.13
B426: JP214.5, U107.12
B427: JP214.4, U107.11
B428: JP214.3, U107.10
B429: JP216.6, U108.13
B430: JP216.5, U108.12
B431: JP216.4, U108.11
B432: JP216.3, U108.10
B433: JP218.6, U109.13
B434: JP218.5, U109.12
B435: JP218.4, U109.11
B436: JP218.3, U109.10
B437: JP220.6, U110.13
B438: JP220.5, U110.12
B439: JP220.4, U110.11
B440: JP220.3, U110.10
B441: JP222.6, U111.13
B442: JP222.5, U111.12
B443: JP222.4, U111.11
B444: JP222.3, U111.10
B445: JP224.6, U112.13
B446: JP224.5, U112.12
B447: JP224.4, U112.11
B448: JP224.3, U112.10
B449: JP226.6, U113.13
B450: JP226.5, U113.12
B451: JP226.4, U113.11
B452: JP226.3, U113.10
B453: JP228.6, U114.13
B454: JP228.5, U114.12
B455: JP228.4, U114.11
B456: JP228.3, U114.10
B457: JP230.6, U115.13
B458: JP230.5, U115.12
B459: JP230.4, U115.11
B460: JP230.3, U115.10
B461: JP232.6, U116.13
B462: JP232.5, U116.12
B463: JP232.4, U116.11
B464: JP232.3, U116.10
B465: JP234.6, U117.13
B466: JP234.5, U117.12
B467: JP234.4, U117.11
B468: JP234.3, U117.10
B469: JP236.6, U118.13
B470: JP236.5, U118.12
B471: JP236.4, U118.11
B472: JP236.3, U118.10
B473: JP238.6, U119.13
B474: JP238.5, U119.12
B475: JP238.4, U119.11
B476: JP238.3, U119.10
B477: JP240.6, U120.13
B478: JP240.5, U120.12
B479: JP240.4, U120.11
B480: JP240.3, U120.10
GND: C1.2, C2.2, JP1.1, JP2.1, U1.7
GND1: C3.2, C4.2, JP3.1, JP4.1, U2.7
GND2: C5.2, C6.2, JP5.1, JP6.1, U3.7
GND3: C7.2, C8.2, JP7.1, JP8.1, U4.7
GND4: C9.2, C10.2, JP9.1, JP10.1, U5.7
GND5: C11.2, C12.2, JP11.1, JP12.1, U6.7
GND6: C13.2, C14.2, JP13.1, JP14.1, U7.7
GND7: C15.2, C16.2, JP15.1, JP16.1, U8.7
GND8: C17.2, C18.2, JP17.1, JP18.1, U9.7
GND9: C19.2, C20.2, JP19.1, JP20.1, U10.7
GND10: C21.2, C22.2, JP21.1, JP22.1, U11.7
GND11: C23.2, C24.2, JP23.1, JP24.1, U12.7
GND12: C25.2, C26.2, JP25.1, JP26.1, U13.7
GND13: C27.2, C28.2, JP27.1, JP28.1, U14.7
GND14: C29.2, C30.2, JP29.1, JP30.1, U15.7
GND15: C31.2, C32.2, JP31.1, JP32.1, U16.7
GND16: C33.2, C34.2, JP33.1, JP34.1, U17.7
GND17: C35.2, C36.2, JP35.1, JP36.1, U18.7
GND18: C37.2, C38.2, JP37.1, JP38.1, U19.7
GND19: C39.2, C40.2, JP39.1, JP40.1, U20.7
GND20: C41.2, C42.2, JP41.1, JP42.1, U21.7
GND21: C43.2, C44.2, JP43.1, JP44.1, U22.7
GND22: C45.2, C46.2, JP45.1, JP46.1, U23.7
GND23: C47.2, C48.2, JP47.1, JP48.1, U24.7
GND24: C49.2, C50.2, JP49.1, JP50.1, U25.7
GND25: C51.2, C52.2, JP51.1, JP52.1, U26.7
GND26: C53.2, C54.2, JP53.1, JP54.1, U27.7
GND27: C55.2, C56.2, JP55.1, JP56.1, U28.7
GND28: C57.2, C58.2, JP57.1, JP58.1, U29.7
GND29: C59.2, C60.2, JP59.1, JP60.1, U30.7
GND30: C61.2, C62.2, JP61.1, JP62.1, U31.7
GND31: C63.2, C64.2, JP63.1, JP64.1, U32.7
GND32: C65.2, C66.2, JP65.1, JP66.1, U33.7
GND33: C67.2, C68.2, JP67.1, JP68.1, U34.7
GND34: C69.2, C70.2, JP69.1, JP70.1, U35.7
GND35: C71.2, C72.2, JP71.1, JP72.1, U36.7
GND36: C73.2, C74.2, JP73.1, JP74.1, U37.7
GND37: C75.2, C76.2, JP75.1, JP76.1, U38.7
GND38: C77.2, C78.2, JP77.1, JP78.1, U39.7
GND39: C79.2, C80.2, JP79.1, JP80.1, U40.7
GND40: C81.2, C82.2, JP81.1, JP82.1, U41.7
GND41: C83.2, C84.2, JP83.1, JP84.1, U42.7
GND42: C85.2, C86.2, JP85.1, JP86.1, U43.7
GND43: C87.2, C88.2, JP87.1, JP88.1, U44.7
GND44: C89.2, C90.2, JP89.1, JP90.1, U45.7
GND45: C91.2, C92.2, JP91.1, JP92.1, U46.7
GND46: C93.2, C94.2, JP93.1, JP94.1, U47.7
GND47: C95.2, C96.2, JP95.1, JP96.1, U48.7
GND48: C97.2, C98.2, JP97.1, JP98.1, U49.7
GND49: C99.2, C100.2, JP99.1, JP100.1, U50.7
GND50: C101.2, C102.2, JP101.1, JP102.1, U51.7
GND51: C103.2, C104.2, JP103.1, JP104.1, U52.7
GND52: C105.2, C106.2, JP105.1, JP106.1, U53.7
GND53: C107.2, C108.2, JP107.1, JP108.1, U54.7
GND54: C109.2, C110.2, JP109.1, JP110.1, U55.7
GND55: C111.2, C112.2, JP111.1, JP112.1, U56.7
GND56: C113.2, C114.2, JP113.1, JP114.1, U57.7
GND57: C115.2, C116.2, JP115.1, JP116.1, U58.7
GND58: C117.2, C118.2, JP117.1, JP118.1, U59.7
GND59: C119.2, C120.2, JP119.1, JP120.1, U60.7
GND60: C121.2, C122.2, JP121.1, JP122.1, U61.7
GND61: C123.2, C124.2, JP123.1, JP124.1, U62.7
GND62: C125.2, C126.2, JP125.1, JP126.1, U63.7
GND63: C127.2, C128.2, JP127.1, JP128.1, U64.7
GND64: C129.2, C130.2, JP129.1, JP130.1, U65.7
GND65: C131.2, C132.2, JP131.1, JP132.1, U66.7
GND66: C133.2, C134.2, JP133.1, JP134.1, U67.7
GND67: C135.2, C136.2, JP135.1, JP136.1, U68.7
GND68: C137.2, C138.2, JP137.1, JP138.1, U69.7
GND69: C139.2, C140.2, JP139.1, JP140.1, U70.7
GND70: C141.2, C142.2, JP141.1, JP142.1, U71.7
GND71: C143.2, C144.2, JP143.1, JP144.1, U72.7
GND72: C145.2, C146.2, JP145.1, JP146.1, U73.7
GND73: C147.2, C148.2, JP147.1, JP148.1, U74.7
GND74: C149.2, C150.2, JP149.1, JP150.1, U75.7
GND75: C151.2, C152.2, JP151.1, JP152.1, U76.7
GND76: C153.2, C154.2, JP153.1, JP154.1, U77.7
GND77: C155.2, C156.2, JP155.1, JP156.1, U78.7
GND78: C157.2, C158.2, JP157.1, JP158.1, U79.7
GND79: C159.2, C160.2, JP159.1, JP160.1, U80.7
GND80: C161.2, C162.2, JP161.1, JP162.1, U81.7
GND81: C163.2, C164.2, JP163.1, JP164.1, U82.7
GND82: C165.2, C166.2, JP165.1, JP166.1, U83.7
GND83: C167.2, C168.2, JP167.1, JP168.1, U84.7
GND84: C169.2, C170.2, JP169.1, JP170.1, U85.7
GND85: C171.2, C172.2, JP171.1, JP172.1, U86.7
GND86: C173.2, C174.2, JP173.1, JP174.1, U87.7
GND87: C175.2, C176.2, JP175.1, JP176.1, U88.7
GND88: C177.2, C178.2, JP177.1, JP178.1, U89.7
GND89: C179.2, C180.2, JP179.1, JP180.1, U90.7
GND90: C181.2, C182.2, JP181.1, JP182.1, U91.7
GND91: C183.2, C184.2, JP183.1, JP184.1, U92.7
GND92: C185.2, C186.2, JP185.1, JP186.1, U93.7
GND93: C187.2, C188.2, JP187.1, JP188.1, U94.7
GND94: C189.2, C190.2, JP189.1, JP190.1, U95.7
GND95: C191.2, C192.2, JP191.1, JP192.1, U96.7
GND96: C193.2, C194.2, JP193.1, JP194.1, U97.7
GND97: C195.2, C196.2, JP195.1, JP196.1, U98.7
GND98: C197.2, C198.2, JP197.1, JP198.1, U99.7
GND99: C199.2, C200.2, JP199.1, JP200.1, U100.7
GND100: C201.2, C202.2, JP201.1, JP202.1, U101.7
GND101: C203.2, C204.2, JP203.1, JP204.1, U102.7
GND102: C205.2, C206.2, JP205.1, JP206.1, U103.7
GND103: C207.2, C208.2, JP207.1, JP208.1, U104.7
GND104: C209.2, C210.2, JP209.1, JP210.1, U105.7
GND105: C211.2, C212.2, JP211.1, JP212.1, U106.7
GND106: C213.2, C214.2, JP213.1, JP214.1, U107.7
GND107: C215.2, C216.2, JP215.1, JP216.1, U108.7
GND108: C217.2, C218.2, JP217.1, JP218.1, U109.7
GND109: C219.2, C220.2, JP219.1, JP220.1, U110.7
GND110: C221.2, C222.2, JP221.1, JP222.1, U111.7
GND111: C223.2, C224.2, JP223.1, JP224.1, U112.7
GND112: C225.2, C226.2, JP225.1, JP226.1, U113.7
GND113: C227.2, C228.2, JP227.1, JP228.1, U114.7
GND114: C229.2, C230.2, JP229.1, JP230.1, U115.7
GND115: C231.2, C232.2, JP231.1, JP232.1, U116.7
GND116: C233.2, C234.2, JP233.1, JP234.1, U117.7
GND117: C235.2, C236.2, JP235.1, JP236.1, U118.7
GND118: C237.2, C238.2, JP237.1, JP238.1, U119.7
GND119: C239.2, C240.2, JP239.1, JP240.1, U120.7
unnamed: JP1.3, U1.5
unnamed: JP1.4, U1.4
unnamed: JP1.5, U1.3
unnamed: JP1.6, U1.2
unnamed: JP3.3, U2.5
unnamed: JP3.4, U2.4
unnamed: JP3.5, U2.3
unnamed: JP3.6, U2.2
unnamed: JP5.3, U3.5
unnamed: JP5.4, U3.4
unnamed: JP5.5, U3.3
unnamed: JP5.6, U3.2
unnamed: JP7.3, U4.5
unnamed: JP7.4, U4.4
unnamed: JP7.5, U4.3
unnamed: JP7.6, U4.2
unnamed: JP9.3, U5.5
unnamed: JP9.4, U5.4
unnamed: JP9.5, U5.3
unnamed: JP9.6, U5.2
unnamed: JP11.3, U6.5
unnamed: JP11.4, U6.4
unnamed: JP11.5, U6.3
unnamed: JP11.6, U6.2
unnamed: JP13.3, U7.5
unnamed: JP13.4, U7.4
unnamed: JP13.5, U7.3
unnamed: JP13.6, U7.2
unnamed: JP15.3, U8.5
unnamed: JP15.4, U8.4
unnamed: JP15.5, U8.3
unnamed: JP15.6, U8.2
unnamed: JP17.3, U9.5
unnamed: JP17.4, U9.4
unnamed: JP17.5, U9.3
unnamed: JP17.6, U9.2
unnamed: JP19.3, U10.5
unnamed: JP19.4, U10.4
unnamed: JP19.5, U10.3
unnamed: JP19.6, U10.2
unnamed: JP21.3, U11.5
unnamed: JP21.4, U11.4
unnamed: JP21.5, U11.3
unnamed: JP21.6, U11.2
unnamed: JP23.3, U12.5
unnamed: JP23.4, U12.4
unnamed: JP23.5, U12.3
unnamed: JP23.6, U12.2
unnamed: JP25.3, U13.5
unnamed: JP25.4, U13.4
unnamed: JP25.5, U13.3
unnamed: JP25.6, U13.2
unnamed: JP27.3, U14.5
unnamed: JP27.4, U14.4
unnamed: JP27.5, U14.3
unnamed: JP27.6, U14.2
unnamed: JP29.3, U15.5
unnamed: JP29.4, U15.4
unnamed: JP29.5, U15.3
unnamed: JP29.6, U15.2
unnamed: JP31.3, U16.5
unnamed: JP31.4, U16.4
unnamed: JP31.5, U16.3
unnamed: JP31.6, U16.2
unnamed: JP33.3, U17.5
unnamed: JP33.4, U17.4
unnamed: JP33.5, U17.3
unnamed: JP33.6, U17.2
unnamed: JP35.3, U18.5
unnamed: JP35.4, U18.4
unnamed: JP35.5, U18.3
unnamed: JP35.6, U18.2
unnamed: JP37.3, U19.5
unnamed: JP37.4, U19.4
unnamed: JP37.5, U19.3
unnamed: JP37.6, U19.2
unnamed: JP39.3, U20.5
unnamed: JP39.4, U20.4
unnamed: JP39.5, U20.3
unnamed: JP39.6, U20.2
unnamed: JP41.3, U21.5
unnamed: JP41.4, U21.4
unnamed: JP41.5, U21.3
unnamed: JP41.6, U21.2
unnamed: JP43.3, U22.5
unnamed: JP43.4, U22.4
unnamed: JP43.5, U22.3
unnamed: JP43.6, U22.2
unnamed: JP45.3, U23.5
unnamed: JP45.4, U23.4
unnamed: JP45.5, U23.3
unnamed: JP45.6, U23.2
unnamed: JP47.3, U24.5
unnamed: JP47.4, U24.4
unnamed: JP47.5, U24.3
unnamed: JP47.6, U24.2
unnamed: JP49.3, U25.5
unnamed: JP49.4, U25.4
unnamed: JP49.5, U25.3
unnamed: JP49.6, U25.2
unnamed: JP51.3, U26.5
unnamed: JP51.4, U26.4
unnamed: JP51.5, U26.3
unnamed: JP51.6, U26.2
unnamed: JP53.3, U27.5
unnamed: JP53.4, U27.4
unnamed: JP53.5, U27.3
unnamed: JP53.6, U27.2
unnamed: JP55.3, U28.5
unnamed: JP55.4, U28.4
unnamed: JP55.5, U28.3
unnamed: JP55.6, U28.2
unnamed: JP57.3, U29.5
unnamed: JP57.4, U29.4
unnamed: JP57.5, U29.3
unnamed: JP57.6, U29.2
unnamed: JP59.3, U30.5
unnamed: JP59.4, U30.4
unnamed: JP59.5, U30.3
unnamed: JP59.6, U30.2
unnamed: JP61.3, U31.5
unnamed: JP61.4, U31.4
unnamed: JP61.5, U31.3
unnamed: JP61.6, U31.2
unnamed: JP63.3, U32.5
unnamed: JP63.4, U32.4
unnamed: JP63.5, U32.3
unnamed: JP63.6, U32.2
unnamed: JP65.3, U33.5
unnamed: JP65.4, U33.4
unnamed: JP65.5, U33.3
unnamed: JP65.6, U33.2
unnamed: JP67.3, U34.5
unnamed: JP67.4, U34.4
unnamed: JP67.5, U34.3
unnamed: JP67.6, U34.2
unnamed: JP69.3, U35.5
unnamed: JP69.4, U35.4
unnamed: JP69.5, U35.3
unnamed: JP69.6, U35.2
unnamed: JP71.3, U36.5
unnamed: JP71.4, U36.4
unnamed: JP71.5, U36.3
unnamed: JP71.6, U36.2
unnamed: JP73.3, U37.5
unnamed: JP73.4, U37.4
unnamed: JP73.5, U37.3
unnamed: JP73.6, U37.2
unnamed: JP75.3, U38.5
unnamed: JP75.4, U38.4
unnamed: JP75.5, U38.3
unnamed: JP75.6, U38.2
unnamed: JP77.3, U39.5
unnamed: JP77.4, U39.4
unnamed: JP77.5, U39.3
unnamed: JP77.6, U39.2
unnamed: JP79.3, U40.5
unnamed: JP79.4, U40.4
unnamed: JP79.5, U40.3
unnamed: JP79.6, U40.2
unnamed: JP81.3, U41.5
unnamed: JP81.4, U41.4
unnamed: JP81.5, U41.3
unnamed: JP81.6, U41.2
unnamed: JP83.3, U42.5
unnamed: JP83.4, U42.4
unnamed: JP83.5, U42.3
unnamed: JP83.6, U42.2
unnamed: JP85.3, U43.5
unnamed: JP85.4, U43.4
unnamed: JP85.5, U43.3
unnamed: JP85.6, U43.2
unnamed: JP87.3, U44.5
unnamed: JP87.4, U44.4
unnamed: JP87.5, U44.3
unnamed: JP87.6, U44.2
unnamed: JP89.3, U45.5
unnamed: JP89.4, U45.4
unnamed: JP89.5, U45.3
unnamed: JP89.6, U45.2
unnamed: JP91.3, U46.5
unnamed: JP91.4, U46.4
unnamed: JP91.5, U46.3
unnamed: JP91.6, U46.2
unnamed: JP93.3, U47.5
unnamed: JP93.4, U47.4
unnamed: JP93.5, U47.3
unnamed: JP93.6, U47.2
unnamed: JP95.3, U48.5
unnamed: JP95.4, U48.4
unnamed: JP95.5, U48.3
unnamed: JP95.6, U48.2
unnamed: JP97.3, U49.5
unnamed: JP97.4, U49.4
unnamed: JP97.5, U49.3
unnamed: JP97.6, U49.2
unnamed: JP99.3, U50.5
unnamed: JP99.4, U50.4
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

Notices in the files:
parts and their libraries:
SparkFun-DigitalIC: Licensing: CC v3.0 Share-Alike You are welcome to use this library for commercial purposes.
SparkFun-Aesthetics: Released under the Creative Commons Attribution Share-Alike 3.0 License
SparkFun-Aesthetics: http://creativecommons.org/licenses/by-sa/3.0
